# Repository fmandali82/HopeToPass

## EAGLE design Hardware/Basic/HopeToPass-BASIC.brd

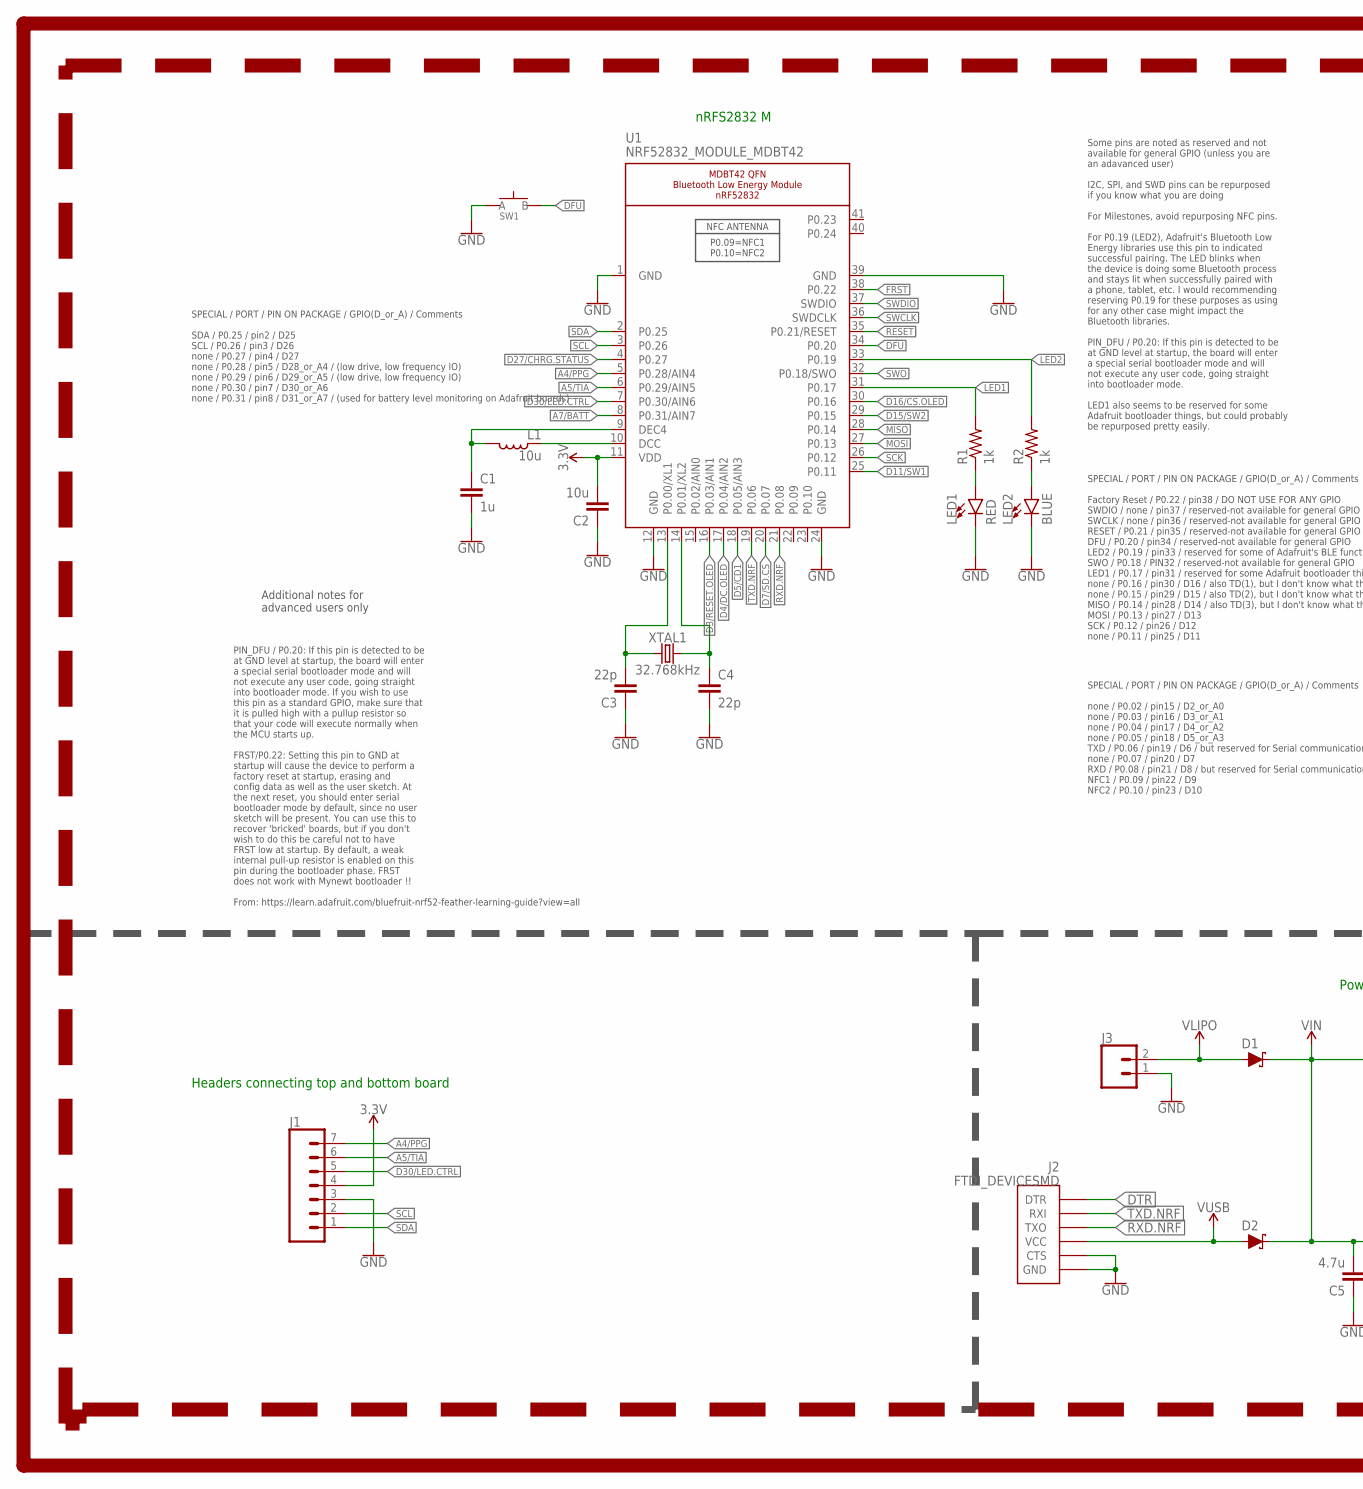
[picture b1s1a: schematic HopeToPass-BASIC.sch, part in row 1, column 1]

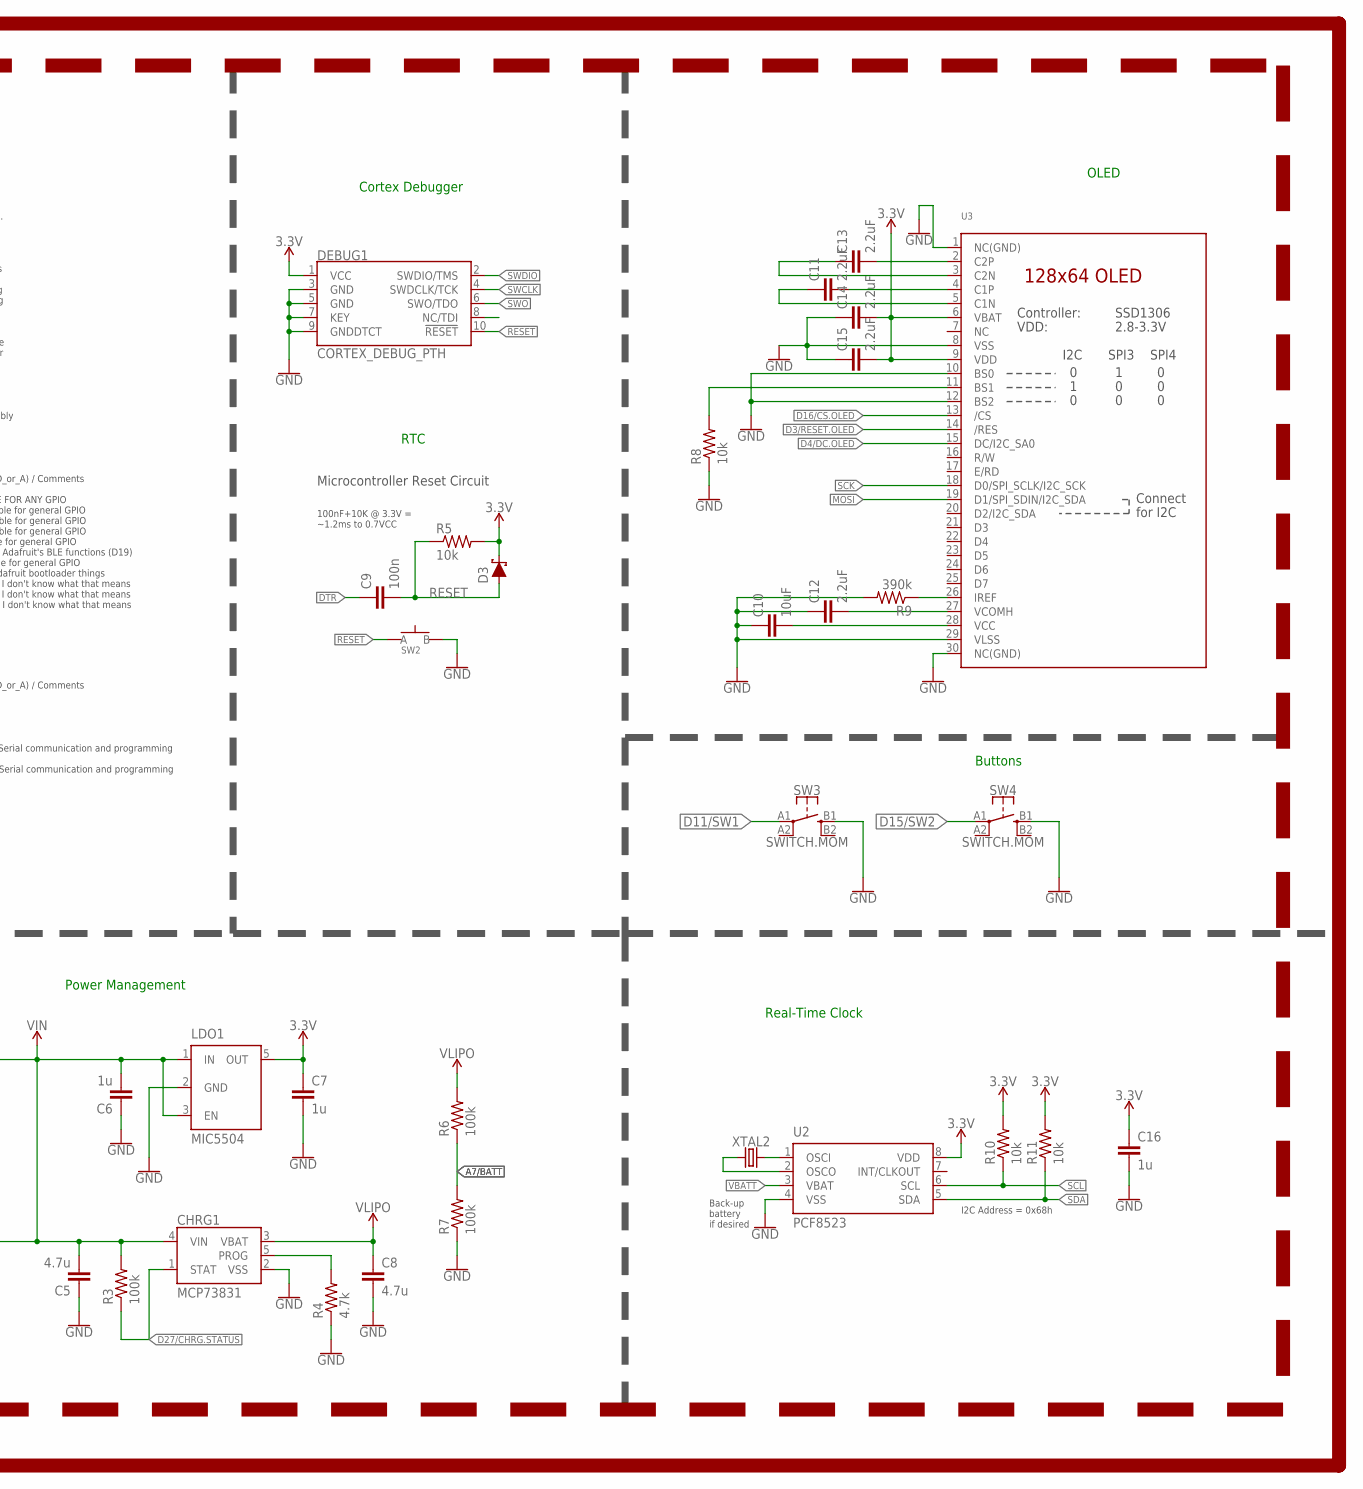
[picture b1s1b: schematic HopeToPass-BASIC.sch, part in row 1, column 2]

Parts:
C1, C6, C7, C16: 1u; C0603
C2: 10u; C0805
C3, C4: 22p; C0603
C5, C8: 4.7u; C0603
C9: 100n; C0603
C10: 10uF; C0603
C11, C12, C13, C14, C15: 2.2uF; C0603
CHRG1: MCP73831; SOT23-5
D1, D2, D3: SCHOTTKY-USC; USC
DEBUG1: CORTEX_DEBUG_PTH; 2X5-PTH-1.27MM
J1: CONN_07-1.27MM; 1X07_1.27MM
J2: FTDI_DEVICESMD; FTDI-SMD
J3: CONN_02; 1X02
L1: 10u; L0603
LDO1: MIC5504; SOT23-5
LED1: RED; LED-0603
LED2: BLUE; LED-0603
R1, R2: 1k; R0603
R3, R6, R7: 100k; R0603
R4: 4.7k; R0603
R5, R8, R10, R11: 10k; R0603
R9: 390k; R0603
SW1, SW2: SPST-PTS830GG140-COPY.1-3; BUTTON-GULLWING
SW3, SW4: SWITCH.MOM; TACTILE_SWITCH_SMD_6.2MM_TALL
U1: NRF52832_MODULE_MDBT42; BLE_MODULE_RAYTAC_MDBT42
U2: PCF8523; SO8; DIGIKEY 568-5306-1-ND
U3: DISP_OLED_UG-2864HSWEG01-NO-WRAPAROUND; UG-2864HSWEG01_0.96IN_NO-WRAPAROUND
XTAL1: 32.768kHz; 2-SMD.NOLEAD.2.0MMTO1.2MM
XTAL2: 32.7680kHz; 2-SMD.NOLEAD.2.0MMTO1.2MM

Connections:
3.3V: C2.2, C7.1, C14.2, C15.2, C16.1, D3.- (C), DEBUG1.1 (VCC), J1.4, LDO1.5 (OUT), R5.2, R10.2, R11.2, U1.11 (VDD), U2.8 (VDD), U3.6 (VBAT), U3.9 (VDD)
A4/PPG: J1.7, U1.5 (P0.28/AIN4)
A5/TIA: J1.6, U1.6 (P0.29/AIN5)
A7/BATT: R6.1, R7.2, U1.8 (P0.31/AIN7)
D3/RESET.OLED: U1.16 (P0.03/AIN1), U3.14 (/RES)
D4/DC.OLED: U1.17 (P0.04/AIN2), U3.15 (DC/I2C_SA0)
D5/CD1: U1.18 (P0.05/AIN3)
D7/SD.CS: U1.20 (P0.07)
D11/SW1: SW3.A1 (1), U1.25 (P0.11)
D15/SW2: SW4.A1 (1), U1.29 (P0.15)
D16/CS.OLED: U1.30 (P0.16), U3.13 (/CS)
D27/CHRG.STATUS: CHRG1.1 (STAT), R3.1, U1.4 (P0.27)
D30/LED.CTRL: J1.5, U1.7 (P0.30/AIN6)
DFU: SW1.3 (B), U1.34 (P0.20)
DTR: C9.1, J2.DTR
FRST: U1.38 (P0.22)
GND: C1.2, C2.1, C3.1, C4.2, C5.1, C6.1, C7.2, C8.2, C10.1, C12.1, C14.1, C15.1, C16.2, CHRG1.2 (VSS), DEBUG1.3 (GND), DEBUG1.5 (GND), DEBUG1.7 (KEY), DEBUG1.9 (GNDDTCT), J1.3, J2.CTS, J2.GND, J3.1, LDO1.2 (GND), LED1.C, LED2.C, R4.1, R7.1, R8.1, R9.2, SW1.1 (A), SW2.3 (B), SW3.B1 (3), SW4.B1 (3), U1.1 (GND), U1.12 (GND), U1.24 (GND), U1.39 (GND), U2.4 (VSS), U3.1 (NC(GND)), U3.8 (VSS), U3.10 (BS0), U3.12 (BS2), U3.29 (VLSS), U3.30 (NC(GND))
LED1: R1.2, U1.31 (P0.17)
LED2: R2.2, U1.33 (P0.19)
MISO: U1.28 (P0.14)
MOSI: U1.27 (P0.13), U3.19 (D1/SPI_SDIN/I2C_SDA)
unnamed: R8.2, U3.11 (BS1)
unnamed: R9.1, U3.26 (IREF)
unnamed: C13.2, U3.2 (C2P)
unnamed: C3.2, U1.13 (P0.00/XL1), XTAL1.P$1 (1)
unnamed: C13.1, U3.3 (C2N)
unnamed: C4.1, U1.14 (P0.01/XL2), XTAL1.P$2 (2)
unnamed: C11.2, U3.4 (C1P)
unnamed: C11.1, U3.5 (C1N)
unnamed: LED1.A, R1.1
unnamed: LED2.A, R2.1
unnamed: L1.1, U1.10 (DCC)
unnamed: C1.1, L1.2, U1.9 (DEC4)
unnamed: C10.2, U3.28 (VCC)
unnamed: C12.2, U3.27 (VCOMH)
unnamed: CHRG1.5 (PROG), R4.2
unnamed: U2.2 (OSCO), XTAL2.P$1 (1)
unnamed: U2.1 (OSCI), XTAL2.P$2 (2)
RESET: C9.2, D3.+ (A), DEBUG1.10 (!RESET), R5.1, SW2.1 (A), U1.35 (P0.21/RESET)
RXD.NRF: J2.TXO, U1.21 (P0.08)
SCK: U1.26 (P0.12), U3.18 (D0/SPI_SCLK/I2C_SCK)
SCL: J1.2, R10.1, U1.3 (P0.26), U2.6 (SCL)
SDA: J1.1, R11.1, U1.2 (P0.25), U2.5 (SDA)
SWCLK: DEBUG1.4 (SWDCLK/TCK), U1.36 (SWDCLK)
SWDIO: DEBUG1.2 (SWDIO/TMS), U1.37 (SWDIO)
SWO: DEBUG1.6 (SWO/TDO), U1.32 (P0.18/SWO)
TXD.NRF: J2.RXI, U1.19 (P0.06)
VBATT: U2.3 (VBAT)
VIN: C5.2, C6.2, CHRG1.4 (VIN), D1.- (C), D2.- (C), LDO1.1 (IN), LDO1.3 (EN), R3.2
VLIPO: C8.1, CHRG1.3 (VBAT), D1.+ (A), J3.2, R6.2
V_USB: D2.+ (A), J2.VCC

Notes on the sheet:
Microcontroller Reset Circuit
100nF+10K @ 3.3V = ~1.2ms to 0.7VCC
SPECIAL / PORT / PIN ON PACKAGE / GPIO(D_or_A) / Comments SDA / P0.25 / pin2 / D25 SCL / P0.26 / pin3 / D26 none / P0.27 / pin4 / D27 none / P0.28 / pin5 / D28_or_A4 / (low drive, low frequency IO) none / P0.29 / pin6 / D29_or_A5 / (low drive, low frequency IO) none / P0.30 / pin7 / D30_or_A6 none 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
SPECIAL / PORT / PIN ON PACKAGE / GPIO(D_or_A) / Comments none / P0.02 / pin15 / D2_or_A0 none / P0.03 / pin16 / D3_or_A1 none / P0.04 / pin17 / D4_or_A2 none / P0.05 / pin18 / D5_or_A3 TXD / P0.06 / pin19 / D6 / but reserved for Serial communication and programming none / P0.07 / pin20 / D7 RXD / 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
SPECIAL / PORT / PIN ON PACKAGE / GPIO(D_or_A) / Comments Factory Reset / P0.22 / pin38 / DO NOT USE FOR ANY GPIO SWDIO / none / pin37 / reserved-not available for general GPIO SWCLK / none / pin36 / reserved-not available for general GPIO RESET / P0.21 / pin35 / reserved-not available for general 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
Some pins are noted as reserved and not available for general GPIO (unless you are an adavanced user) I2C, SPI, and SWD pins can be repurposed if you know what you are doing For Milestones, avoid repurposing NFC pins. For P0.19 (LED2), Adafruit's Bluetooth Low Energy libraries use this pin to indic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
PIN_DFU / P0.20: If this pin is detected to be at GND level at startup, the board will enter a special serial bootloader mode and will not execute any user code, going straight into bootloader mode. If you wish to use this pin as a standard GPIO, make sure that it is pulled high with a pullup resis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
Additional notes for advanced users only
nRFS2832 M
OLED
Power Management
Buttons
Real-Time Clock
Cortex Debugger
RTC
Headers connecting top and bottom board
I2C Address = 0x68h
Back-up battery if desired

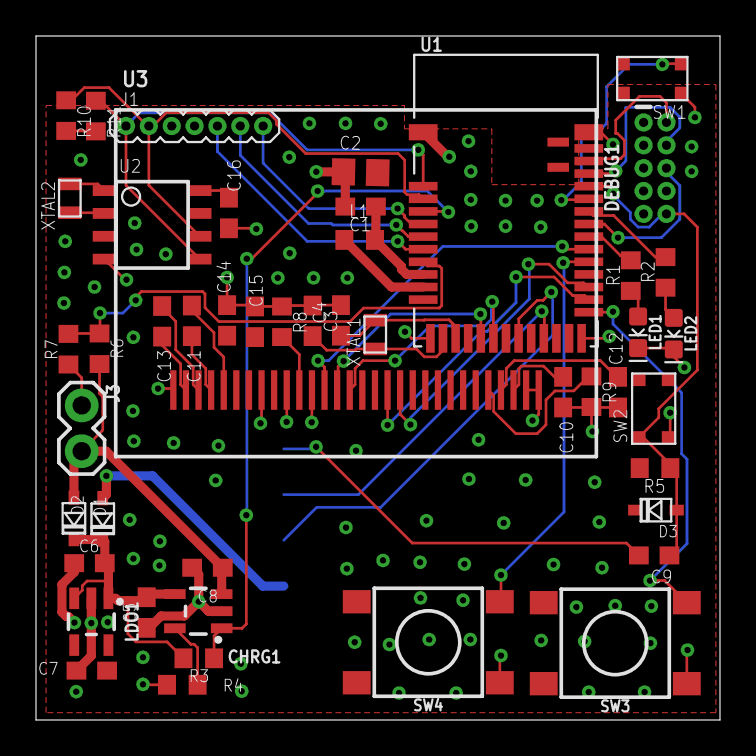
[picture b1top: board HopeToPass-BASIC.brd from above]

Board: 2 copper layers, 38.0 x 38.0 mm, 48 parts (1 on the bottom side), 46 nets.

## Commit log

2022-09-07 Adding word file
2022-09-14 Initial Repo Organization
2022-09-15 Started working on board
2022-09-22 Complete eagle 001 and started programming
2022-10-17 10/16 updates
2022-10-19 Completed Routing the board
2022-11-02 orlando renumbered components
2022-11-02 added more ground vias and generated gerbers
2022-11-03 BOM completed partially
